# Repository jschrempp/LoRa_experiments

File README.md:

# LoRa_experiments
## Tests of LoRA module (RYLR998) ranging and low power.

The Reyax RYLR998 is an inexpensive LoRa "modem".  It can perform point to point wireless data communication with other such modules.

The RYLR998 contains both a LoRa chip and a low power microcontroller.  A host microcontroller communicates with an RLYR998 using
serial port "AT" commands, making the RYLR998 very easy to use.  In addition, the RYLR998 has a low power sleep mode that reduces current
draw to about 10 microamps.  The use of LoRa for long distance, low volume data communication along with the ability to sleep the module
when not transmitting suggests that these modules could be ideal for use as long range contact open/close sensors.

The purpose of the tests documented in this repository is to explore the RYLR998 module capabilities in two respects:

- Long range operation:  the ability of the module to successfully commmunicate from an outdoor location some distance from a house
into a receiver located inside of the house.

- Low power operation:  the ability of the module to be powered down when not needed to transmit a short message, in support
of battery powered operation.

There are two main folders in this repository:

- Range_Testing: this folder contains a report and source code for range testing experiments.

- Low_Power_Testing: this folder contains a report and source code for testing low power operation of the module. It also contains
a spreadsheet to calculate battery life, based upon using an Attiny85 as the host microcontroller with a reset pulse generator circuit 
to power it up for transmitting a short message and then powering the LoRa module down and then powering itself down until the next reset.

## LoRa set up ##
- LoRa AT command guide https://lemosint.com/wp-content/uploads/2021/11/Lora_AT_Command_RYLR998_RYLR498_EN.pdf
- LoRa module we use https://reyax.com/products/RYLR498

Note that for these tests you need to program each LoRa module by hand using a terminal emulator and an FTDI module. Connect four
pins from the FTDI to the LoRa module (leave the reset pin on the LoRa module unconnected):

```
FTDI       LoRa
3v3        VDD
TXD        RXD
RXD        TXD
GND        GND
```

Plug the FTDI device into your laptop.

You can use the Arduino IDE Serial Monitor. With the IDE running go to Tools / Port and select the port of your FTDI device (it might be 
something like `/dev/serial-1`). Then click the Serial Monitor button on the upper right of the Arduino IDE. This brings up a new window.
In the bottom menu select "Both NL & CR" and "115200 baud". In the command window at the top type AT and click Send. You should get the 
response +OK

Assuming you are now connected correctly to your LoRa module, perform the following commands:
```
AT+ADDRESS=0
AT+NETWORKID=3
```
Do the same for your second LoRa module.

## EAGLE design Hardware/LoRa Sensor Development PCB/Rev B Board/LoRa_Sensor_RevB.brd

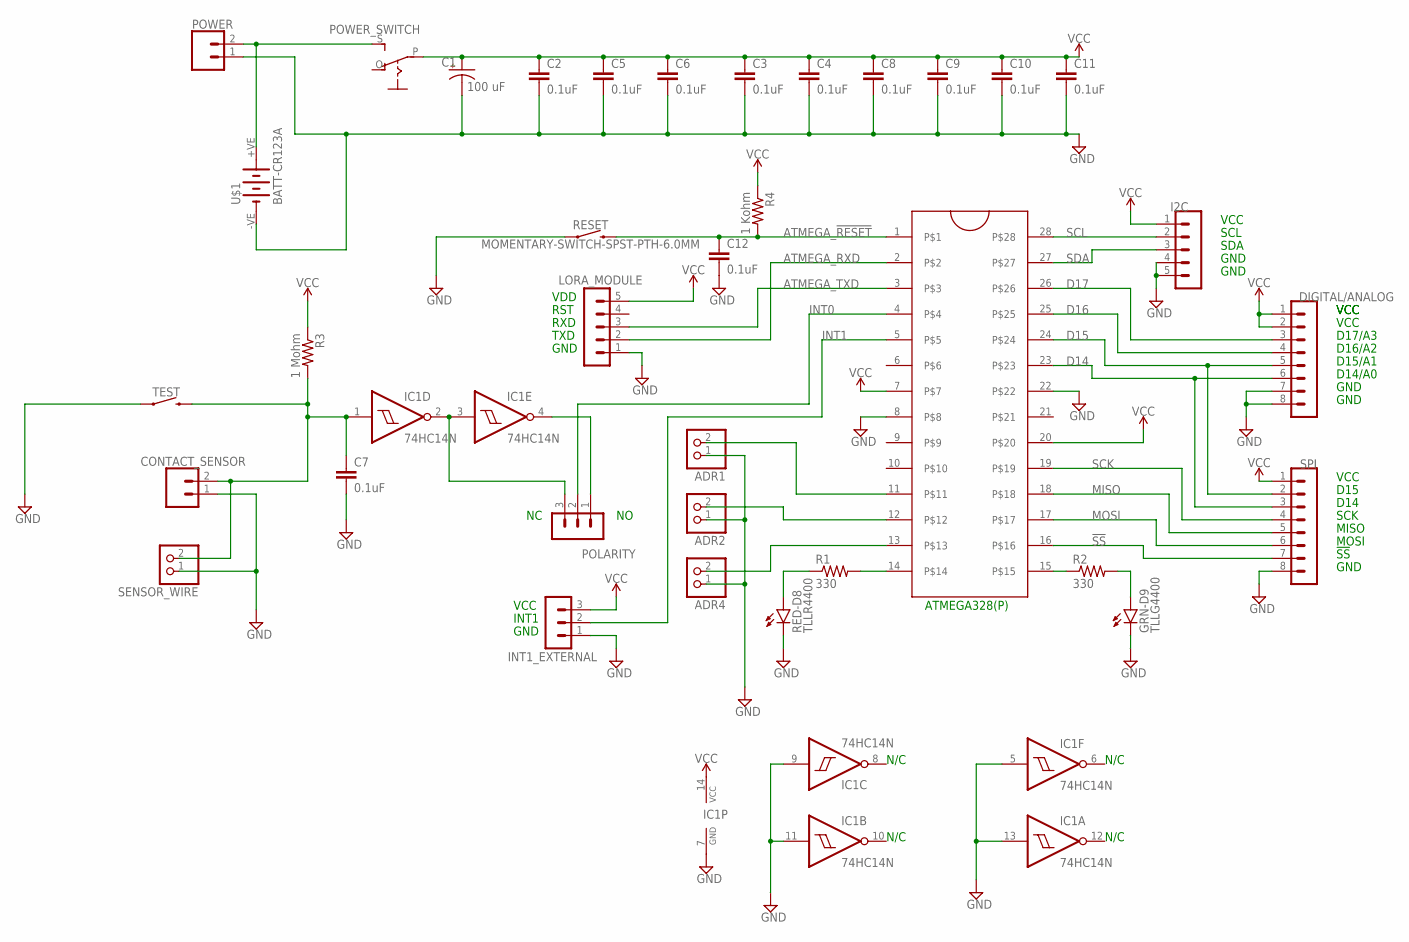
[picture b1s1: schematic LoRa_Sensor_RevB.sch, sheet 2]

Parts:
ADR1, ADR2, ADR4: PINHD-1X2; 1X02
C1: 100 uF; E2,5-6
C2, C3, C4, C5, C6, C7, C8, C9, C10, C11, C12: 0.1uF; CAP-PTH-SMALL-KIT
CONTACT_SENSOR: CONN_023.5MM; SCREWTERMINAL-3.5MM-2
DIGITAL/ANALOG: MA08-1
GRN-D9: TLLG4400; LED3MM
I2C: MA05-1
IC1: 74HC14N; DIL14
INT1_EXTERNAL: MA03-1
J1: ZIFSOCKET-28-3"; DIL28-3-ZIF_SOCKET
LORA_MODULE: MA05-1
POLARITY: MA03-1
POWER: CONN_023.5MM; SCREWTERMINAL-3.5MM-2
POWER_SWITCH: EG1218S; EG1218
R1, R2: 330; 0309/12
R3: 1 Mohm; 0309/12
R4: 1 Kohm; 0309/12
RED-D8: TLLR4400; LED3MM
RESET: MOMENTARY-SWITCH-SPST-PTH-6.0MM; TACTILE_SWITCH_PTH_6.0MM
SENSOR_WIRE: PINHD-1X2; 1X02
SPI: MA08-1
TEST: MOMENTARY-SWITCH-SPST-PTH-6.0MM; TACTILE_SWITCH_PTH_6.0MM
U$1: BATT-CR123A; KEYSTONE-2/3A

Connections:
!SS: J1.16, SPI.7
ATMEGA_!RESET: C12.1, J1.1, R4.2, RESET.3 (2)
ATMEGA_RXD: J1.2, LORA_MODULE.2
ATMEGA_TXD: J1.3, LORA_MODULE.3
D14: DIGITAL/ANALOG.6, J1.23, SPI.3
D15: DIGITAL/ANALOG.5, J1.24, SPI.2
D16: DIGITAL/ANALOG.4, J1.25
D17: DIGITAL/ANALOG.3, J1.26
GND: ADR1.1, ADR2.1, ADR4.1, C1.-, C2.2, C3.2, C4.2, C5.2, C6.2, C7.2, C8.2, C9.2, C10.2, C11.2, C12.2, CONTACT_SENSOR.1, DIGITAL/ANALOG.7, DIGITAL/ANALOG.8, GRN-D9.K (C), I2C.4, I2C.5, IC1.5 (I), IC1.7 (GND), IC1.9 (I), IC1.11 (I), IC1.13 (I), INT1_EXTERNAL.1, J1.8, J1.22, LORA_MODULE.1, POWER.1, RED-D8.K (C), RESET.1, SENSOR_WIRE.1, SPI.8, TEST.1, U$1.-VE (-)
INT0: J1.4, POLARITY.2
INT1: INT1_EXTERNAL.2, J1.5
MISO: J1.18, SPI.5
MOSI: J1.17, SPI.6
unnamed: C7.1, CONTACT_SENSOR.2, IC1.1 (I), R3.2, SENSOR_WIRE.2, TEST.3 (2)
unnamed: POWER.2, POWER_SWITCH.S, U$1.+VE (+)
unnamed: J1.15, R2.1
unnamed: GRN-D9.A, R2.2
unnamed: J1.14, R1.2
unnamed: R1.1, RED-D8.A
unnamed: ADR4.2, J1.13
unnamed: IC1.2 (O), IC1.3 (I), POLARITY.3
unnamed: IC1.4 (O), POLARITY.1
unnamed: ADR2.2, J1.12
unnamed: ADR1.2, J1.11
SCK: J1.19, SPI.4
SCL: I2C.2, J1.28
SDA: I2C.3, J1.27
VCC: C1.+, C2.1, C3.1, C4.1, C5.1, C6.1, C8.1, C9.1, C10.1, C11.1, DIGITAL/ANALOG.1, DIGITAL/ANALOG.2, I2C.1, IC1.14 (VCC), INT1_EXTERNAL.3, J1.7, J1.20, LORA_MODULE.5, POWER_SWITCH.P, R3.1, R4.1, SPI.1

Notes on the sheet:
GND
TXD
RXD
RST
VDD
N/C
ATMEGA328(P)
VCC
INT1
SCL
SDA
D16/A2
D15/A1
D14/A0
D17/A3
D15
D14
SCK
MISO
MOSI
!SS

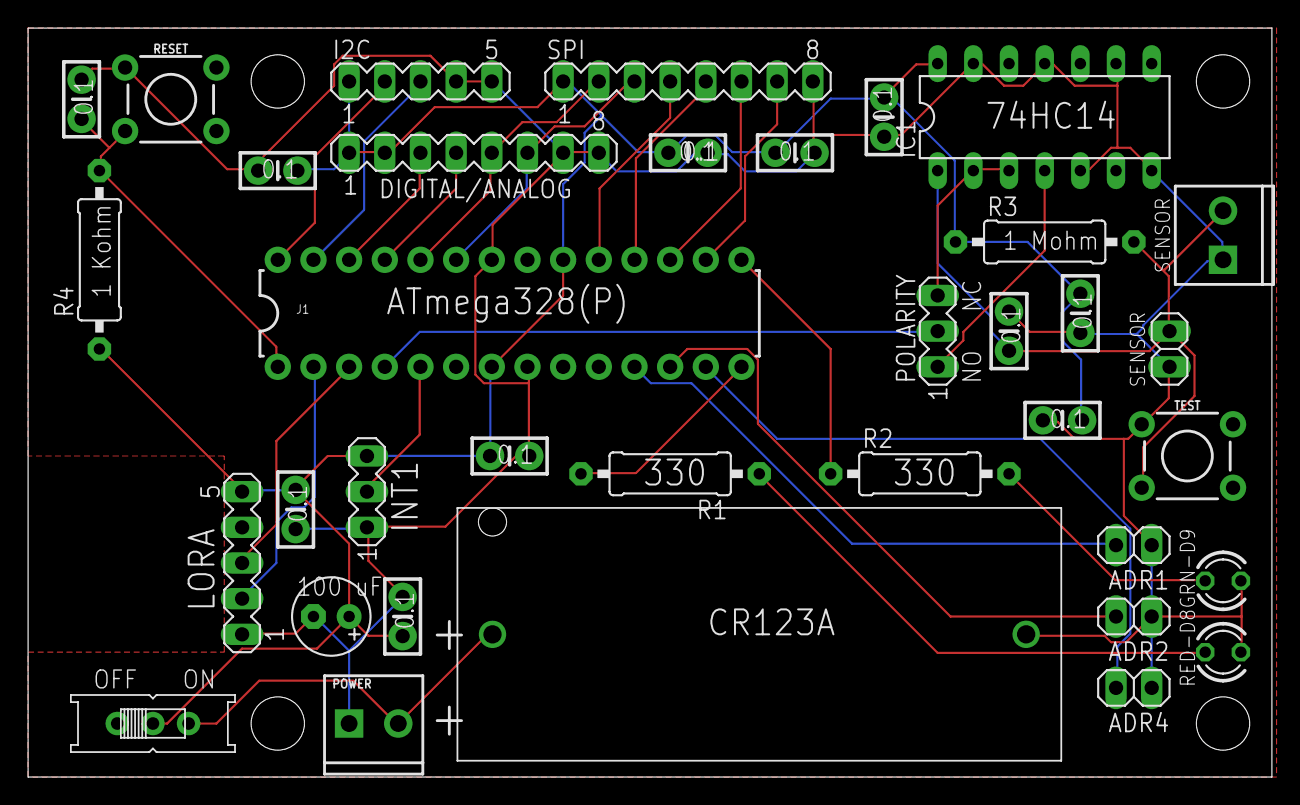
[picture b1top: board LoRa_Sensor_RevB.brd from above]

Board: 2 copper layers, 88.6 x 53.3 mm, 36 parts (0 on the bottom side), 28 nets.

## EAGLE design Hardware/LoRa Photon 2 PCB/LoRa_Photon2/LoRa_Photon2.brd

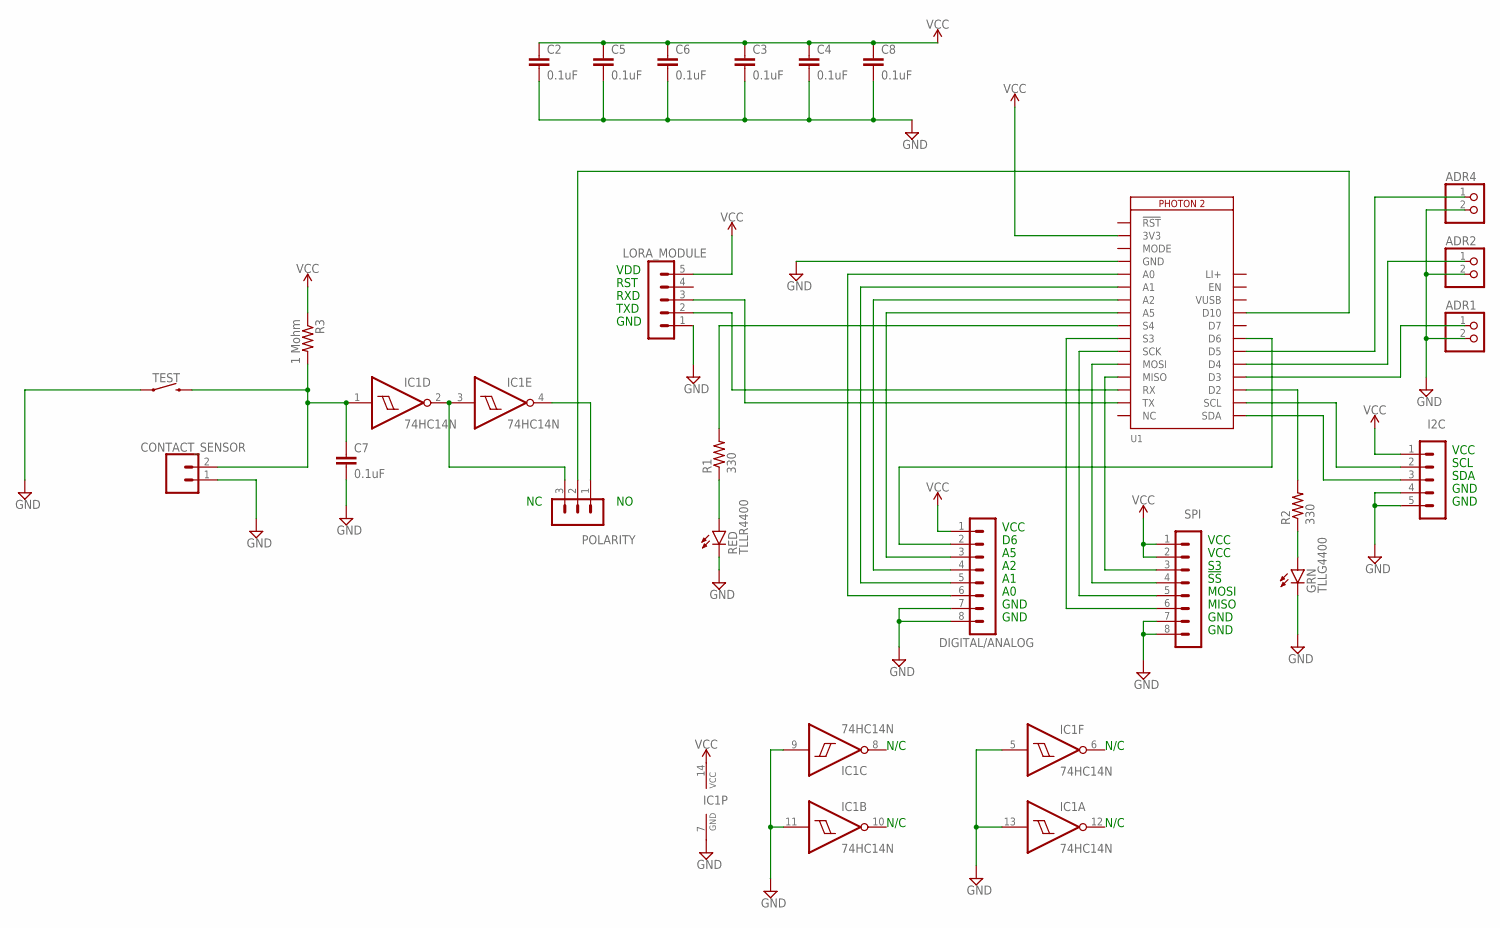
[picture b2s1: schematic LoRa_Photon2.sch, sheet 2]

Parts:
ADR1, ADR2, ADR4: PINHD-1X2; 1X02
C2, C3, C4, C5, C6, C7, C8: 0.1uF; CAP-PTH-SMALL-KIT
CONTACT_SENSOR: CONN_023.5MM; SCREWTERMINAL-3.5MM-2
DIGITAL/ANALOG: MA08-1
GRN: TLLG4400; LED3MM
I2C: MA05-1
IC1: 74HC14N; DIL14
LORA_MODULE: MA05-1
POLARITY: MA03-1
R1, R2: 330; 0309/12
R3: 1 Mohm; 0309/12
RED: TLLR4400; LED3MM
SPI: MA08-1
TEST: MOMENTARY-SWITCH-SPST-PTH-6.0MM; TACTILE_SWITCH_PTH_6.0MM
U1: PHOTON2

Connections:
GND: ADR1.2, ADR2.2, ADR4.2, C2.2, C3.2, C4.2, C5.2, C6.2, C7.2, C8.2, CONTACT_SENSOR.1, DIGITAL/ANALOG.7, DIGITAL/ANALOG.8, GRN.K (C), I2C.4, I2C.5, IC1.5 (I), IC1.7 (GND), IC1.9 (I), IC1.11 (I), IC1.13 (I), LORA_MODULE.1, RED.K (C), SPI.7, SPI.8, TEST.1, U1.4 (GND)
LI+: U1.28 (LI+)
unnamed: C7.1, CONTACT_SENSOR.2, IC1.1 (I), R3.2, TEST.3 (2)
unnamed: LORA_MODULE.3, U1.15 (TX)
unnamed: GRN.A, R2.1
unnamed: R2.2, U1.19 (D2)
unnamed: R1.2, U1.9 (S4)
unnamed: R1.1, RED.A
unnamed: ADR4.1, U1.22 (D5)
unnamed: IC1.2 (O), IC1.3 (I), POLARITY.3
unnamed: IC1.4 (O), POLARITY.1
unnamed: I2C.2, U1.18 (SCL)
unnamed: ADR2.1, U1.21 (D4)
unnamed: LORA_MODULE.2, U1.14 (RX)
unnamed: I2C.3, U1.17 (SDA)
unnamed: POLARITY.2, U1.25 (D10)
unnamed: ADR1.1, U1.20 (D3)
unnamed: SPI.3, U1.13 (MISO)
unnamed: SPI.4, U1.12 (MOSI)
unnamed: SPI.5, U1.11 (SCK)
unnamed: SPI.6, U1.10 (S3)
unnamed: DIGITAL/ANALOG.2, U1.23 (D6)
unnamed: DIGITAL/ANALOG.3, U1.8 (A5)
unnamed: DIGITAL/ANALOG.4, U1.7 (A2)
unnamed: DIGITAL/ANALOG.5, U1.6 (A1)
unnamed: DIGITAL/ANALOG.6, U1.5 (A0)
VCC: C2.1, C3.1, C4.1, C5.1, C6.1, C8.1, DIGITAL/ANALOG.1, I2C.1, IC1.14 (VCC), LORA_MODULE.5, R3.1, SPI.1, SPI.2, U1.2 (3V3)
VUSB: U1.26 (VUSB)

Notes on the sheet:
GND
TXD
RXD
RST
VDD
N/C
VCC
SCL
SDA
MISO
MOSI
!SS

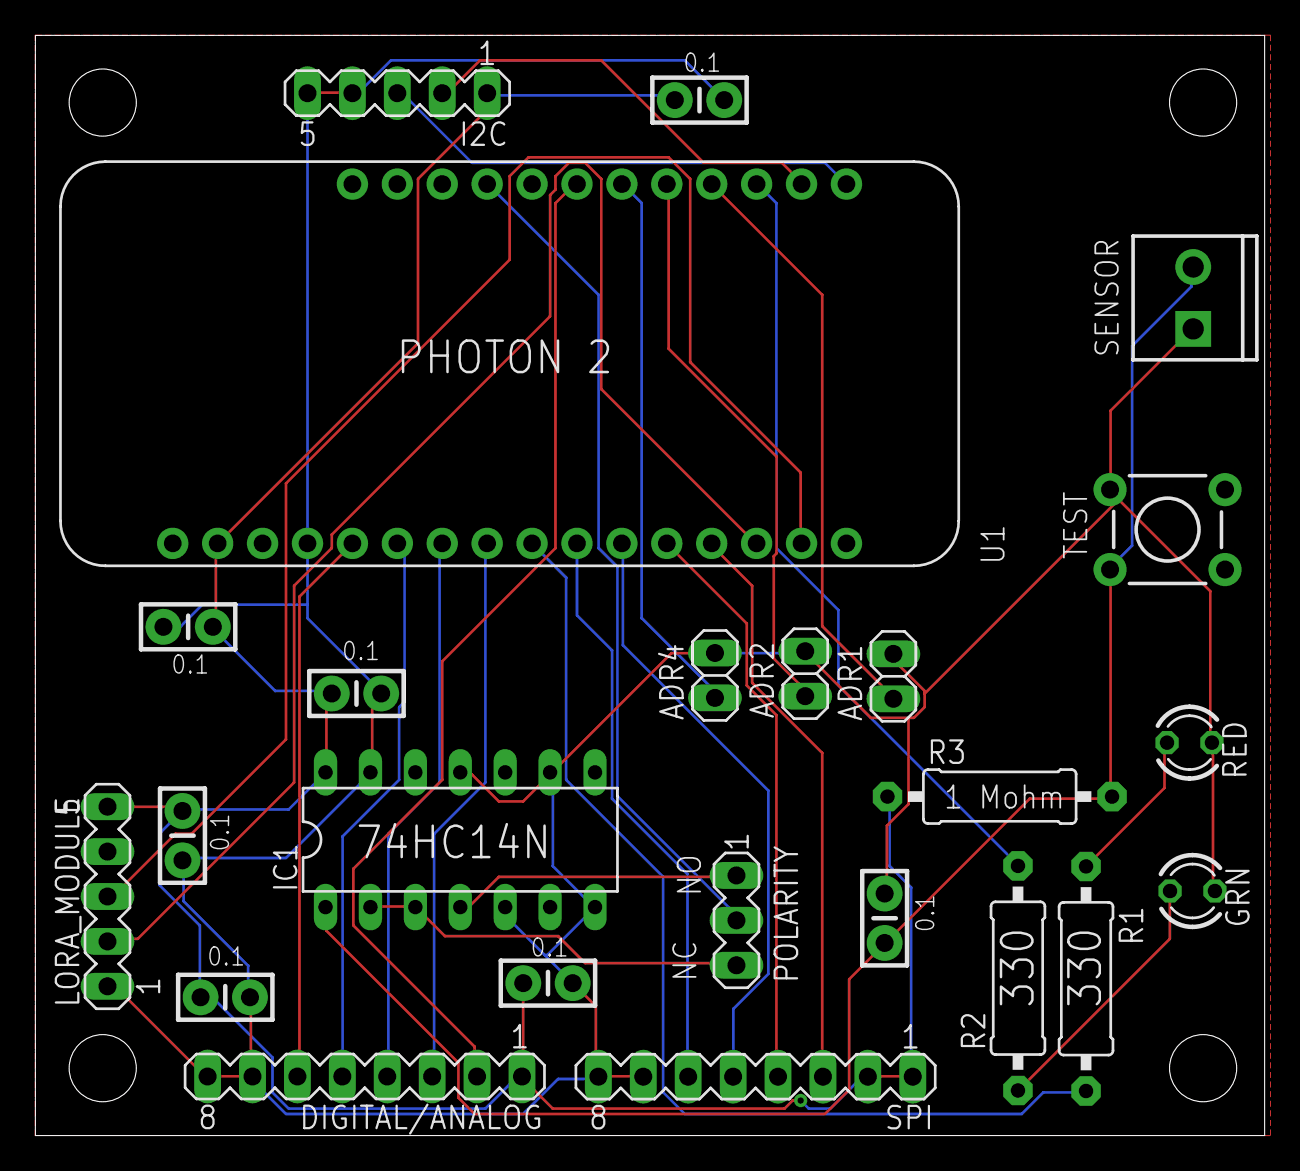
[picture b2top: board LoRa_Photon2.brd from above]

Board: 2 copper layers, 69.5 x 62.2 mm, 24 parts (0 on the bottom side), 26 nets.

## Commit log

2024-04-25 Changed test for received data
2024-05-04 Added code for low power testing
2024-05-05 Create Battery power calculations.xlsx
    Calculation of battery life assuming use of an Attiny85 microcontroller and a reset pulse generator circuit based upon 74HC1322 IC
2024-07-05 Update README.md
    added link to AT commands
2024-07-06 Update README.md
    added LoRa setup info
2024-07-06 Update README.md
    added link to LoRa module
2024-07-06 LoRa configuration
2024-07-07 config is our default
2024-07-07 changes to make sensor report more quickly
2024-07-07 ignore the cpp shadow file
2024-07-10 hub responds with error messages; sensor blinks them out
2024-07-31 Hub logs to google sheet
2024-07-31 using tpp_LoRa
2024-07-31 the header file too
2024-07-31 variable timeout on LoRa commands
2024-08-01 Capture parameters when reading lora status
2024-08-01 send lora params with message 1
2024-08-01 catch up to new version tpp_LoRa
2024-08-01 trim receivedData from LoRa
2024-08-01 a host of small debugging aids
2024-08-01 brought up to date
2024-08-01 debug now optional. LoRa timeout is better
2024-08-01 works
2024-08-01 updated tpp_LoRa
2024-08-03 LoRa parameters are set each time we boot
2024-08-03 updated to new tpp_LoRa
2024-08-04 Added ATmega328 low power testing code
    Changed the folder name for the LoRa module low power testing to make this clear. Added folder for Arduino code that tests low power code for ATmega328.
2024-08-05 Update Interrupt_Test2_Low_Power.ino
    Changed to use external pullup rather than internal pullup. Quiescent power supply draw when contact is closed is reduced from 85 microamps to about 3.4 microamps.
2024-08-06 device address now used by hub. clean up in tpp_LoRa.cpp
2024-08-06 with hub address of 57248
2024-08-07 moved to current tpp library
2024-08-07 updated tpp library
2024-08-07 minor cleanup
2024-08-07 update to current version
2024-08-08 small bug affecting payload of first message
2024-08-08 better handling of start up errors
2024-08-08 new tpp_lora, better start up error handling
2024-08-08 better error handling on startup
2024-08-10 fix to work with Photon 1
2024-08-10 update to latest tpp_lora
2024-08-11 removed a comment
2024-08-11 added a busy flag to help with multiple active sensors
2024-08-11 renamed module global variable
2024-08-12 Create Basic_ATmega328_LoRa_test.ino
    This is essentially the same test that was performed using a Photon on 5/24. It now uses the bare bones ATmega328. It powers up and down the LoRa module but does not power down the ATmega328 chip.
2024-08-12 Update Basic_ATmega328_LoRa_test.ino
    Added another LoRa power up command to ensure that we get a +OK response after LoRa power down
2024-08-14 Create Low_power_ATmega328_LoRa_integration.ino
    Version 1.0 of integration of microcontroller low power and LoRa into a functionaing contact clouse sensor.
2024-08-14 set radio power explictly; log RSSI
2024-08-16 added device UID
2024-08-16 first two messages now contain config info
2024-08-18 updated comments
2024-08-18 went to 9,11,1,24 for best range reception
2024-08-18 added UID to first message
2024-08-24 Particle webhook for logging
2024-08-24 ignore arduino stuff
2024-09-11 sketchbook folder for ATMega work
2024-09-14 hub receives message ok but sensor blinks 7 error on answer from hub
2024-09-22 hub gets good msg, sensor does not get RCV from LoRa
2024-09-27 this works but is not pretty
2024-09-27 works, still not pretty
2024-10-01 ported from Arduino. works in Photon2
2024-10-26 Development PCB
    Added a HARDWARE folder and placed design for a development board PCB into this folder. Eagle CAD files and manufacturing files are all included.
2024-11-02 Dev PCB Photos
    The Dev PCB is shown assembled and in a successful test configuration.
2024-11-03 Update Low_power_ATmega328_LoRa_integration.ino
    Added support for both red and green LEDs.
2024-11-04 Update Low_power_ATmega328_LoRa_integration.ino
    Added 500 ms delay after LoRa transmission and before putting the LoRa module to sleep. Updated comments up front and bumped the version to 1.20.
2024-11-13 Update Low_power_ATmega328_LoRa_integration.ino
    Commented out the delay for testing. Tests OK.
2024-11-14 set LoRa serial to 38400
2024-11-14 Went to default LoRa config values
2024-11-15 d0 is now used to set lora device address on boot
2024-11-15 changed order of LoRa params to match LoRa report of params. Avoids confusion.
2024-11-16 Added ATMega programming instructions
    Added pdf document to Hardware folder.
2024-12-05 works on P2
2024-12-06 works on P2 sensor
2024-12-06 still works on P2 sensor
2024-12-08 works on both P2 and ATmega328
2024-12-08 file cleanup
2024-12-09 Added Arduino code
    Added the 4 files to a folder called RangeTestSensor inside of the arduinoSketchbook folder. The code does not compile because of #if and if() statements which should probably be #ifdef statements, b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
2024-12-09 Update tpp_LoRaGlobals.h
    Fixed the #define issue in the globals file. Now the code compiles!
2024-12-11 after code review. works on P2
2024-12-11 verified on ATmega
2024-12-12 LoRa now sleeps. Works on P2
2024-12-12 LoRa power down works on ATMega
2024-12-12 more low power, works on P2
2024-12-12 button press is now an ISR. Works on P2
2024-12-13 works on P2 and ATMega328
2024-12-13 P2 and ATmega tested. works
2024-12-14 ATmega now runs at least 300 transactions
2024-12-14 removed continuous running test code
2024-12-15 Hub updated to new tpp_LoRa.
2024-12-15 improved status message a bit
2024-12-15 removing old files
2024-12-15 minor changes
2024-12-15 final changes to low memory. note no LoRa powerdown
2024-12-16 Version 1.30
    Changed the sensor trip message to be short and to have a one-up message number (mod 10) so that we can detect messed messages at the hub or upstream thereof.
2024-12-16 Update Low_power_ATmega328_LoRa_integration.ino
    Changed reserved buffer size to 32 - counted wrong before.
2024-12-18 version 1.40
    Added computation and setting of the LoRa module device address based upon a defined base address + offset; the offset being determined by 3 jumpers (Arduino pins 12, 11, 10 as MSB - LSB). Also used 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
2024-12-19 Created a Photon Based Tester
    This tester uses the TPP Wireless I/O Board to stress test the LoRa sensor. The relay on the Wireless I/O Board is closed and opened a pre-determined number of times. The Hub logs the received messag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
2024-12-19 Update LoRa_Sensor_Tester.ino
    Changed to run 1000 sensor trips for stress testing.
2024-12-19 ran on ATmega for 1150 transactions
2024-12-21 includes ATMega power down
2024-12-21 added comment v2.4
2024-12-21 tested on P2 for 10 transactions
2024-12-21 v2.4 minor changes for P2 compilation
2024-12-22 added setAddress to only set dev address on LoRa
2024-12-22 Added support for address jumpers
    Address jumpers are now processed in the code. Changed setAdrress() argument type to unsigned int in all files. Added pin definitions to globals.h file.
    This code should work on the Photon 2 as well as on Arduino, but it has only been tested on Arduino. These files need to be copied into the VS locations for Photon.
2024-12-25 Test version 2.6.1 of Arduino
    Added sending a reset test message at the end of setup() so that any resets during stress testing will be logged. This is temporary code for stress testing the production sensor code on ATMega328 onl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
2024-12-26 address lines work on P2
2024-12-26 #define to not wait for hub response
2024-12-26 2.8 works on ATMega328
2024-12-26 messages are now short
2024-12-27 added pinSetDriveStrength
2024-12-27 added from device address to debug message
2024-12-28 Added Phoiton 2 datasheet to Hardware
2024-12-28 Set ATMega328 Sensor to not wait for response
    Only change is to defined constant for testing with no waiting for a response from the hub.
2025-01-10 Rev A PCB files added
2025-01-14 CRFOP is now a config item in .h file
2025-01-16 Update tpp_LoRaGlobals.h
    Changed the Address jumper pins to correspond to the rev A1 pcb.
2025-01-17 resolved P2 issue with debug printing
2025-01-26 Update settings.json
    Changed the hub to use Photon 2
2025-01-26 P2 based hub code fixes
    I changed the pin definitions to the latest spec. Also corrected typo in #include. Pin changes in tpp_LoRaGlobals.h. Typo change in RangeTestSensor.ino.
2025-01-26 Added Eagle file for Photon 2 PCB
    These files are preliminary. The board layout is not done.
2025-02-01 Added Photon 2 PCB
    Added Eagle files, schematic pdf and rendering of the board to the Hardware folder.
2025-02-02 works on ATMega sensor
2025-02-02 we should not check in vscode/settings
2025-02-02 moved tpp_LoRa from Sketchbook to Hub
2025-02-02 removing settings.json from github
2025-02-02 added vscode settings to gitignore
2025-02-18 Minor changes to schematic
    Only changed labels on schematic. Does not alter the netlist or the board layout.
2025-03-13 merged in ATmega code. works on P2, but not debug msgs
2025-03-15 Rev B PCB
    Rev B PCB is complete and off to manufacturing. This board is a little longer than Rev A, but should otherwise be mechanically compatible. It includes an onboard battery.
2025-04-03 Programming Bare Bones ATMega document
    Uploaded PDF version of this instruction manual.
2025-04-09 changed default CFROP
    Is was set as 10; should be 22 for max power. Changed to 22.
2025-04-18 added case 3D files
2025-06-07 Version 3.0
    Added a cloud function to send simulated sensor events to the Particle cloud. Also added a cloud variable to read out the current code version for maintenance purposes.
2025-06-07 Update settings.json
    Updated OS to 6.3.0 (Prerelease)
2025-06-08 AI2 App
    Added source and installation files for an Android app to play administrative voice clips using version 3.0 of the Hub.
2025-06-24 help button case
2025-06-25 Updated Admin App
    Added additional buttons and deviceIDs

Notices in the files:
Hardware/LoRa Photon 2 PCB/LoRa_Photon2/LoRa_Photon2.brd:
(c) 2025, ALL RIGHTS RESERVED
Hardware/LoRa Sensor Development PCB/Rev B Board/LoRa_Sensor_RevB.brd:
(c) 2025, Team Practical Projects, All Rights Reserved
parts and their libraries:
SparkFun-Capacitors: Licensing: Creative Commons ShareAlike 4.0 International - https://creativecommons.org/licenses/by-sa/4.0
Particle-Devices: Licensing: Designed by Particle.
